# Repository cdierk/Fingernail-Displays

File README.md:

# Fingernail-Displays

## Hardware notes
The pink board is a [Teensy 3.2](https://www.pjrc.com/teensy/index.html). Here's the [pinout.](https://www.pjrc.com/teensy/pinout.html)

The tiny red epaper breakout board is from [this hackaday project.](https://hackaday.io/project/13327-teensy-e-paper-adapter-board).

## Software notes
The [code for the red e-paper breakout board is here,](https://github.com/jarek319/EPD215). Note that it was designed w/ an older pin layout, so you need to swap two of the pins as per [this issue on github.](https://github.com/jarek319/EPD215/issues/4).
Specifically, 

### Annotations
Difference between SPI and SWSPI is d1 and d0 are set to output in SWSPI.

Power on the cog driver:
```
initScreen()
...
  digitalWrite( _rs, HIGH );        //RES# = 1    <-----
  delay( 1 );                       //Delay 1ms          \
  digitalWrite( _cs, HIGH );        //CS# = 1      <---- these two lines power on the cog driver.

  Serial.println( "Waiting for busy signal" );
  while ( digitalRead( _bs ) == HIGH ); //Make sure BUSY = LOW      <---- first step of initializing COG driver.
```
[source](https://github.com/jarek319/EPD215/blob/e8205ba3651f23074bca707f821be8e2f3143674/EPD215.cpp#L281)
[download datasheet, pg. 10 of datasheet](http://www.pervasivedisplays.com/LiteratureRetrieve.aspx?ID=232068)

#### Testing
pin setup (SPI)
EPD215(17, 16, 14, 15)
Output: https://www.dropbox.com/s/jrkega85on69x7t/Screenshot%202017-12-15%2012.04.25.png?dl=0

EPD215(17, 16, 15, 14)

## Code to upload bitmap images

0. If you're using [this adapter board and a Teensy, as here,](https://hackaday.io/project/13327-teensy-e-paper-adapter-board) follow these steps.
1. Download [EPD215 library from here.](https://github.com/jarek319/EPD215). Those instructions will also have you install the [Adafruit GFX library.](https://github.com/adafruit/Adafruit-GFX-Library)
2.

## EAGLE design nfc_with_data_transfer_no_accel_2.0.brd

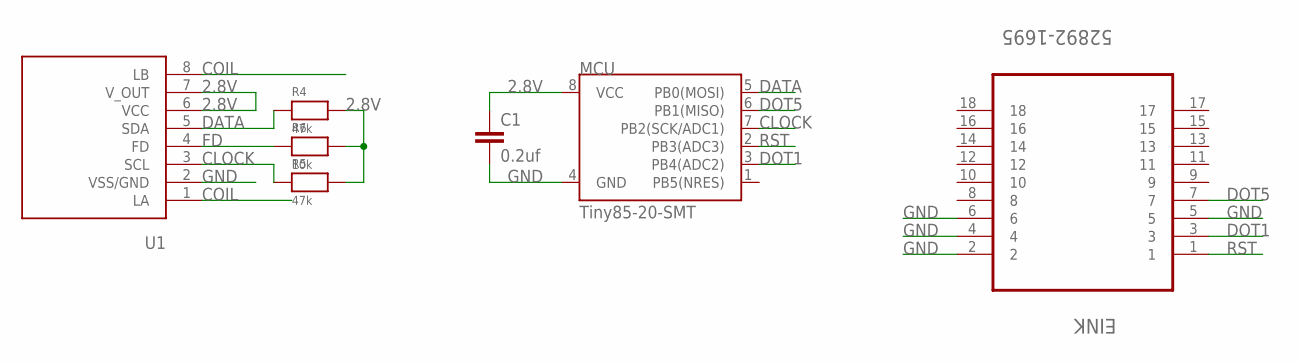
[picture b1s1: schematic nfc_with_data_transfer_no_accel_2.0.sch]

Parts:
C1: 0.2uf; 1206
EINK: 52892-1695; MOLEX_52892-1695
MCU: Tiny85-20-SMT; SO08-EIAJ
R4, R5: 47k; 0603
R6: 10k; 0603
U1: NT3H1101

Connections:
2.8V: C1.1, MCU.8 (VCC), R4.2, R5.2, R6.2, U1.6 (VCC), U1.7 (V_OUT)
CLOCK: MCU.7 (PB2(SCK/ADC1)), R5.1, U1.3 (SCL)
COIL: U1.1 (LA), U1.8 (LB)
DATA: MCU.5 (PB0(MOSI)), R4.1, U1.5 (SDA)
DOT1: EINK.3, MCU.3 (PB4(ADC2))
DOT5: EINK.7, MCU.6 (PB1(MISO))
FD: R6.1, U1.4 (FD)
GND: C1.2, EINK.2, EINK.4, EINK.5, EINK.6, MCU.4 (GND), U1.2 (VSS/GND)
RST: EINK.1, MCU.2 (PB3(ADC3))

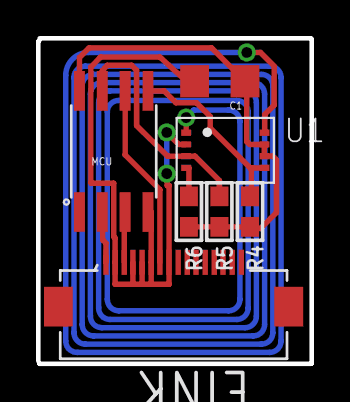
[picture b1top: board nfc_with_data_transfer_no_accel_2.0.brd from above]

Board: 2 copper layers, 15.2 x 18.1 mm, 7 parts (0 on the bottom side), 9 nets.

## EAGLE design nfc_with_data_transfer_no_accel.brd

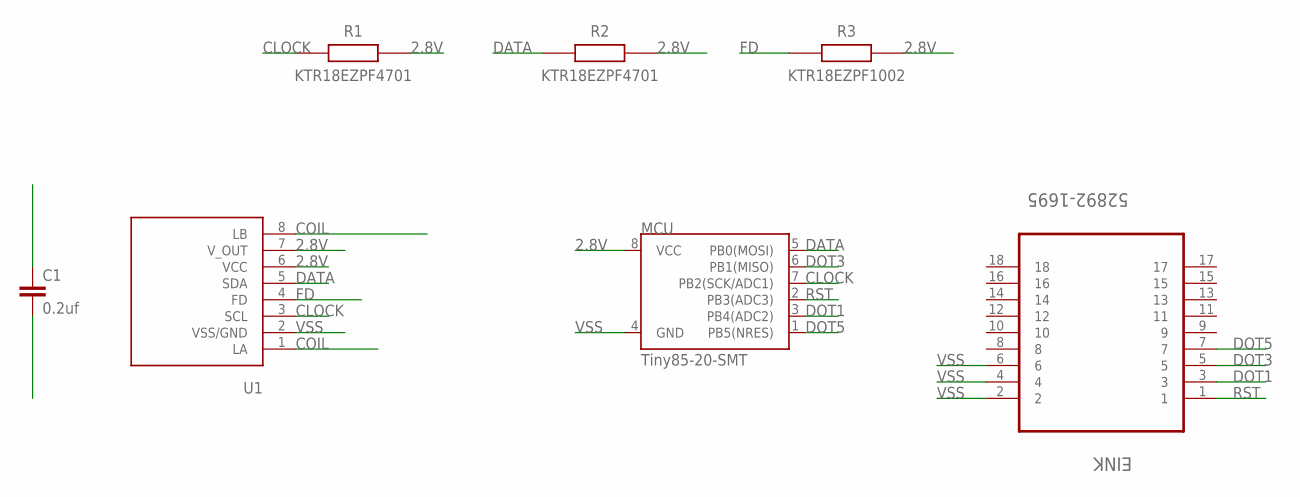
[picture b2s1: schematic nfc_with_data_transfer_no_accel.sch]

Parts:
C1: 0.2uf; 1206
EINK: 52892-1695; MOLEX_52892-1695
MCU: Tiny85-20-SMT; SO08-EIAJ
R1, R2: KTR18EZPF4701; RESC3216X65N
R3: KTR18EZPF1002; RESC3216X65N
U1: NT3H1101

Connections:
2.8V: C1.1, MCU.8 (VCC), R1.2, R2.2, R3.2, U1.6 (VCC), U1.7 (V_OUT)
CLOCK: MCU.7 (PB2(SCK/ADC1)), R1.1, U1.3 (SCL)
COIL: U1.1 (LA), U1.8 (LB)
DATA: MCU.5 (PB0(MOSI)), R2.1, U1.5 (SDA)
DOT1: EINK.3, MCU.3 (PB4(ADC2))
DOT3: EINK.5, MCU.6 (PB1(MISO))
DOT5: EINK.7
FD: R3.1, U1.4 (FD)
RST: EINK.1, MCU.2 (PB3(ADC3))
VSS: C1.2, EINK.2, EINK.4, EINK.6, MCU.4 (GND), U1.2 (VSS/GND)

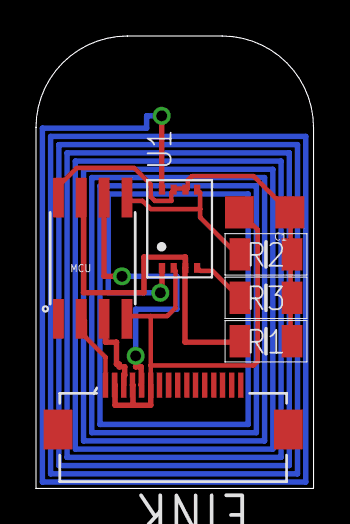
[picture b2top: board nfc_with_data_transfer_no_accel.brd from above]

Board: 2 copper layers, 15.4 x 25.1 mm, 7 parts (0 on the bottom side), 9 nets.

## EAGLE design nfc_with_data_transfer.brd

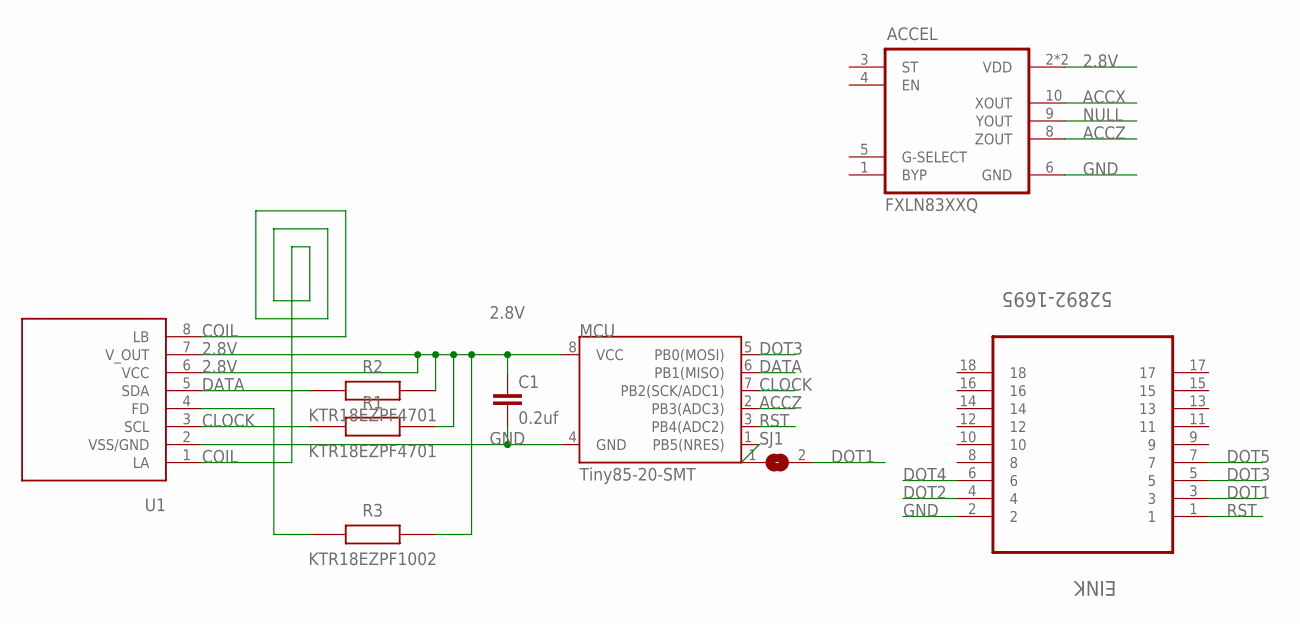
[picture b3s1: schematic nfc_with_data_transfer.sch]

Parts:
ACCEL: FXLN83XXQ; QFN12-3X3
C1: 0.2uf; 1206
EINK: 52892-1695; MOLEX_52892-1695
MCU: Tiny85-20-SMT; SO08-EIAJ
R1, R2: KTR18EZPF4701; RESC3216X65N
R3: KTR18EZPF1002; RESC3216X65N
SJ1: SOLDERJUMPER; SOLDERJUMPER_ARROW_NOPASTE
U1: NT3H1101

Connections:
2.8V: ACCEL.2 (VDD), ACCEL.7 (VDD), C1.1, MCU.8 (VCC), R1.2, R2.2, R3.2, U1.6 (VCC), U1.7 (V_OUT)
ACCX: ACCEL.10 (XOUT)
ACCZ: ACCEL.8 (ZOUT), MCU.2 (PB3(ADC3))
CLOCK: MCU.7 (PB2(SCK/ADC1)), U1.3 (SCL)
COIL: U1.1 (LA), U1.8 (LB)
DATA: MCU.6 (PB1(MISO)), U1.5 (SDA)
DOT1: EINK.3, SJ1.2
DOT2: EINK.4
DOT3: EINK.5, MCU.5 (PB0(MOSI))
DOT4: EINK.6
DOT5: EINK.7
GND: ACCEL.6 (GND), C1.2, EINK.2, MCU.4 (GND), U1.2 (VSS/GND)
unnamed: MCU.1 (PB5(NRES)), SJ1.1
unnamed: R3.1, U1.4 (FD)
NULL: ACCEL.9 (YOUT)
RST: EINK.1, MCU.3 (PB4(ADC2))

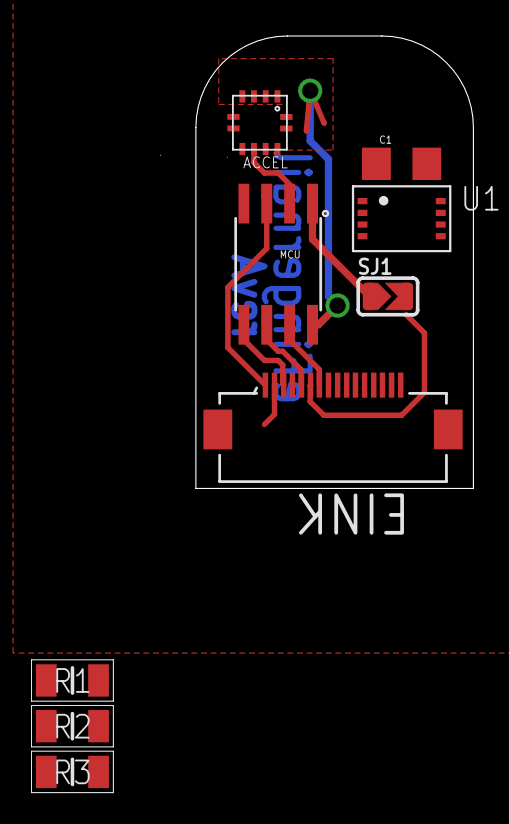
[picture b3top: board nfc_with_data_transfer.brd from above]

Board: 2 copper layers, 15.4 x 25.1 mm, 9 parts (0 on the bottom side), 11 nets.

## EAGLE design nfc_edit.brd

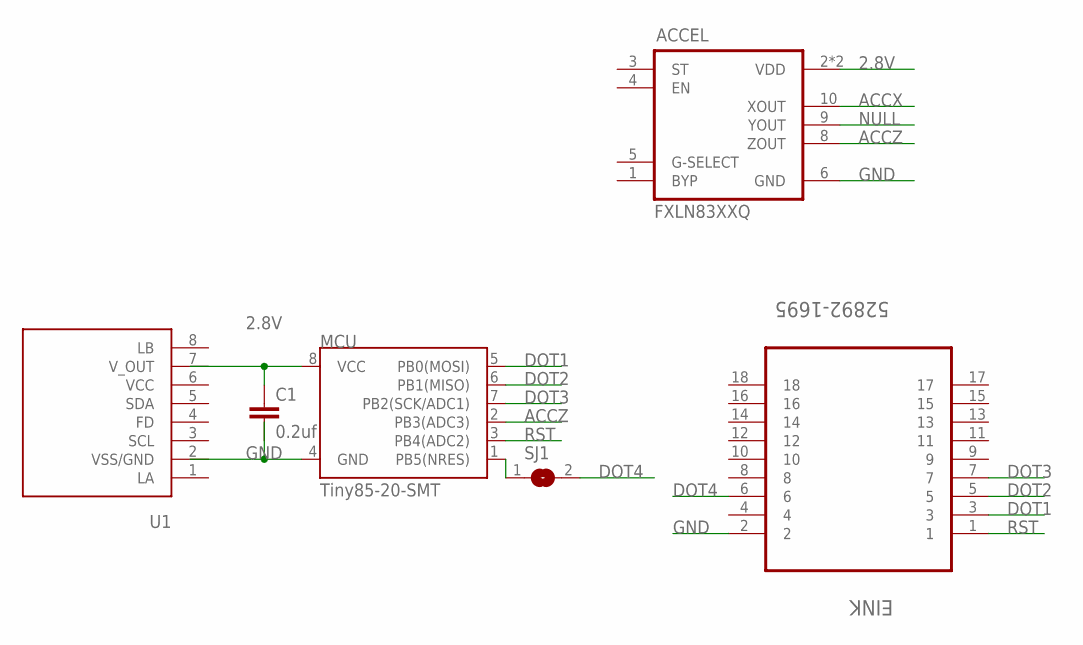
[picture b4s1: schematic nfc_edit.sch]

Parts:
ACCEL: FXLN83XXQ; QFN12-3X3
C1: 0.2uf; 1206
EINK: 52892-1695; MOLEX_52892-1695
MCU: Tiny85-20-SMT; SO08-EIAJ
SJ1: SOLDERJUMPER; SOLDERJUMPER_ARROW_NOPASTE
U1: NT3H1101

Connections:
2.8V: ACCEL.2 (VDD), ACCEL.7 (VDD), C1.1, MCU.8 (VCC), U1.7 (V_OUT)
ACCX: ACCEL.10 (XOUT)
ACCZ: ACCEL.8 (ZOUT), MCU.2 (PB3(ADC3))
DOT1: EINK.3, MCU.5 (PB0(MOSI))
DOT2: EINK.5, MCU.6 (PB1(MISO))
DOT3: EINK.7, MCU.7 (PB2(SCK/ADC1))
DOT4: EINK.6, SJ1.2
GND: ACCEL.6 (GND), EINK.2, MCU.4 (GND)
unnamed: MCU.1 (PB5(NRES)), SJ1.1
NULL: ACCEL.9 (YOUT)
RST: EINK.1, MCU.3 (PB4(ADC2))
VCC: U1.6 (VCC)
VSS/GND: U1.2 (VSS/GND)

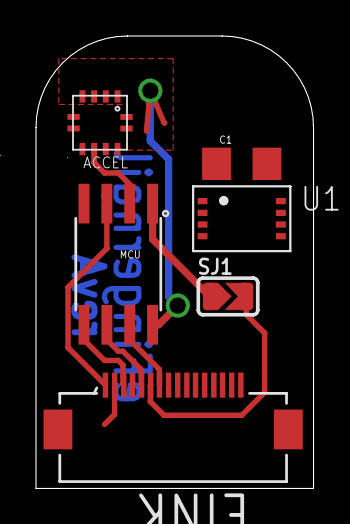
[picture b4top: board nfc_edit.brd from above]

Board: 2 copper layers, 15.4 x 25.1 mm, 6 parts (0 on the bottom side), 9 nets.

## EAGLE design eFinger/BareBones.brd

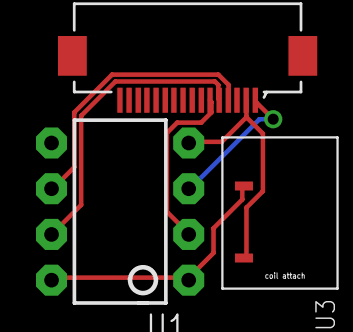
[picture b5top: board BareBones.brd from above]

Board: 2 copper layers, 3 parts (0 on the bottom side), 7 nets.

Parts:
U1: TINY85-20-DIP; DIP08
U2: 52892-1695; MOLEX_52892-1695
U3: P9027LP-R

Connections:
unnamed: U1.3, U2.1
unnamed: U1.2, U2.6
unnamed: U1.1, U1.8, U3.OUT
unnamed: U1.4, U2.2, U3.P$2
unnamed: U1.5, U2.3
unnamed: U1.6, U2.4
unnamed: U1.7, U2.5

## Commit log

2016-08-08 First Commit: ATTiny + Shift Register + Eink + Accelerometer
    Accelerometer code not quite working
2016-08-08 Adding Eagle files
    These Eagle files contain ATTiny, IDT Receiver circuit (rough placement
    of pads), and FPC connector only.
2016-08-08 Added Shift Register to Eagle schematic
    Haven’t drawn connections from Shift Register to FPC, but should be
    straight forward. Also haven’t added Accelerometer, not sure which one
    to use—need to order
2016-08-15 Accelerometer code working
    Binary count only when accelerometer is tilted in the -x direction
2016-09-06 Accelerometer and connections added to Eagle file
2016-09-06 Eagle part library for IDT Power Receiver
2016-09-14 AlterNail Code: Pick a Design
    Code with updated pin connections (to match circuitry). Alternates
    between 1 dot and 3 dots depending on vibration (uses simple
    thresholding)
2016-09-15 Alternail_usage added
    Code for points/usage/counter application of AlterNail
2016-11-08 latest board
2017-04-29 Replaced Wireless Power Kit with NFC chip
    Updated schematic and board with NT3H1101 nfc chip in place of IDT wireless reference kit. AlterNail.lbr includes a custom package for this part (NT3H1101). The datasheet for NT3H1101 recommends plac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
2017-04-29 .2uF capacitor has been added
    NFC added and connected via power only (no data transfer with ATTiny85)
2017-04-29 give up 2 pins on ATTiny for I2C
    connected nfc chip (with .2uf capacitor). gave up 2 pins on ATTiny for I2C. Still control middle dot and potentially top dot with reset pin.
2017-05-01 Added suggested resistors
    Added 4k7 pull-up resistors on SCL and SDA pins. Also added 10 kOhm pull-up resistor on Field Detection line.
2017-05-01 Library files for added resistors
2017-05-02 Updated ATTiny85 pin connections, removed accel
    updated pin connections for I2C (data & clock), removed the accelerometer
2017-05-02 Updated board (with traces and embedded coil)
2017-05-04 fixed rst
2017-05-04 final
2017-05-23 latest without top ground plane
2017-05-29 Tweaks by Eric to produce first manufactured board
2017-05-29 no message
2017-09-09 Latest fingernail code (i2c -> display)
    The most recent fingernail code in which the ATTiny85 reads block 0x01 of NT3H1101 user memory. The ATTiny85 then updates the e-ink display with the corresponding design. This code allows for seamles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
2017-09-09 Arduino code for dynamic wearable displays
    Reads a value from i2c and then sets the connected eink display to the corresponding image
2017-09-10 BitMaps for E-ink
2017-09-11 Corresponding JPG files for XBM
2017-09-14 Updated catverse files
2017-09-14 Added Fitts_1_9

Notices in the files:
parts and their libraries:
SparkFun-DigitalIC: Licensing: Creative Commons ShareAlike 4.0 International - https://creativecommons.org/licenses/by-sa/4.0
microbuilder: This work is placed in the public domain, and may be freely used for commercial and non-commercial work with the following conditions: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
